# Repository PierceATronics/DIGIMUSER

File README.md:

# DIGIMUSER
DIGIMUSER is a digital vocal effect processor "stompbox" that applies a variety of real-time signal processing algorithms to alter the voice of a singer. DIGIMUSER takes a (1/4)" mono jack input from a dynamic microphone and outputs through another (1/4)" cable to an amplifier or to additional audio processing equipment. Since the effects applied by DIGIMUSER are performed digitally on a microcontroller, it can be reprogrammed to implement a wide collection of effecus such as filters, delays, distortions, and spatial effects. A standard bypass stomp button enables and disables the effect, a knob selects the type of applied effect, and a slider controls the intensity of the effect.
 
## Project Team Members
David Pierce Walker-Howell (EE), Luke kennard (COMPE), Danielle Stewart (COMPE), Suaod Alhajry (EE), Angel Martinez (COMPE)

## Contribute to this Project
Here are the guidelines to contribute to the project.

#### Branching
The development process for software or hardware must be done in a seperate branch from **main**. Once a software or hardware component is completed a pull request must be made before merging with **main**. The pull request must reviewed and approved before merging to main. 

Here is how to create a new branch off of main. Please use the following naming format for the branch **[Your_name]_[description_of_branch]**

```
Example

//Creates a new branch called "Pierce_I2S_software_development" off of the "main" branch
git checkout -b Pierce_I2S_software_development main
```

#### GIT workflow
Be sure to keep your branch (and the Repository) up-to-date on your local machine by performing pulls often (i.e. be sure to make a pull of the repo prior to making any new edits or commits). Also make sure to commit changes locally often and push those commits to the Github Repository often as well. Below is the typical workflow to follow

```
//Open a git bash or linux terminal and move to the DIGIMUSER project director

//You hop on your computer to begin working on the DIGIMUSER
//First, make sure to pull the repo

git pull

//Next, make sure you are in your development branch

git branch [THE_BRANCH_YOUR_ARE_DEVELOPING_IN]

//Work on coding and designing like on awesome engineer.

//Now you are at a good saving point, and would like to take a break for the day
//Commit your changes with a nice message about what you added/edited

git commit -m "Reworked the communication code for faster data transfer"

//You also want to save your code to the Github repo. So push those commits to the repo

git push origin [THE_BRANCH_YOU_ARE_DEVELOPING_IN]

```

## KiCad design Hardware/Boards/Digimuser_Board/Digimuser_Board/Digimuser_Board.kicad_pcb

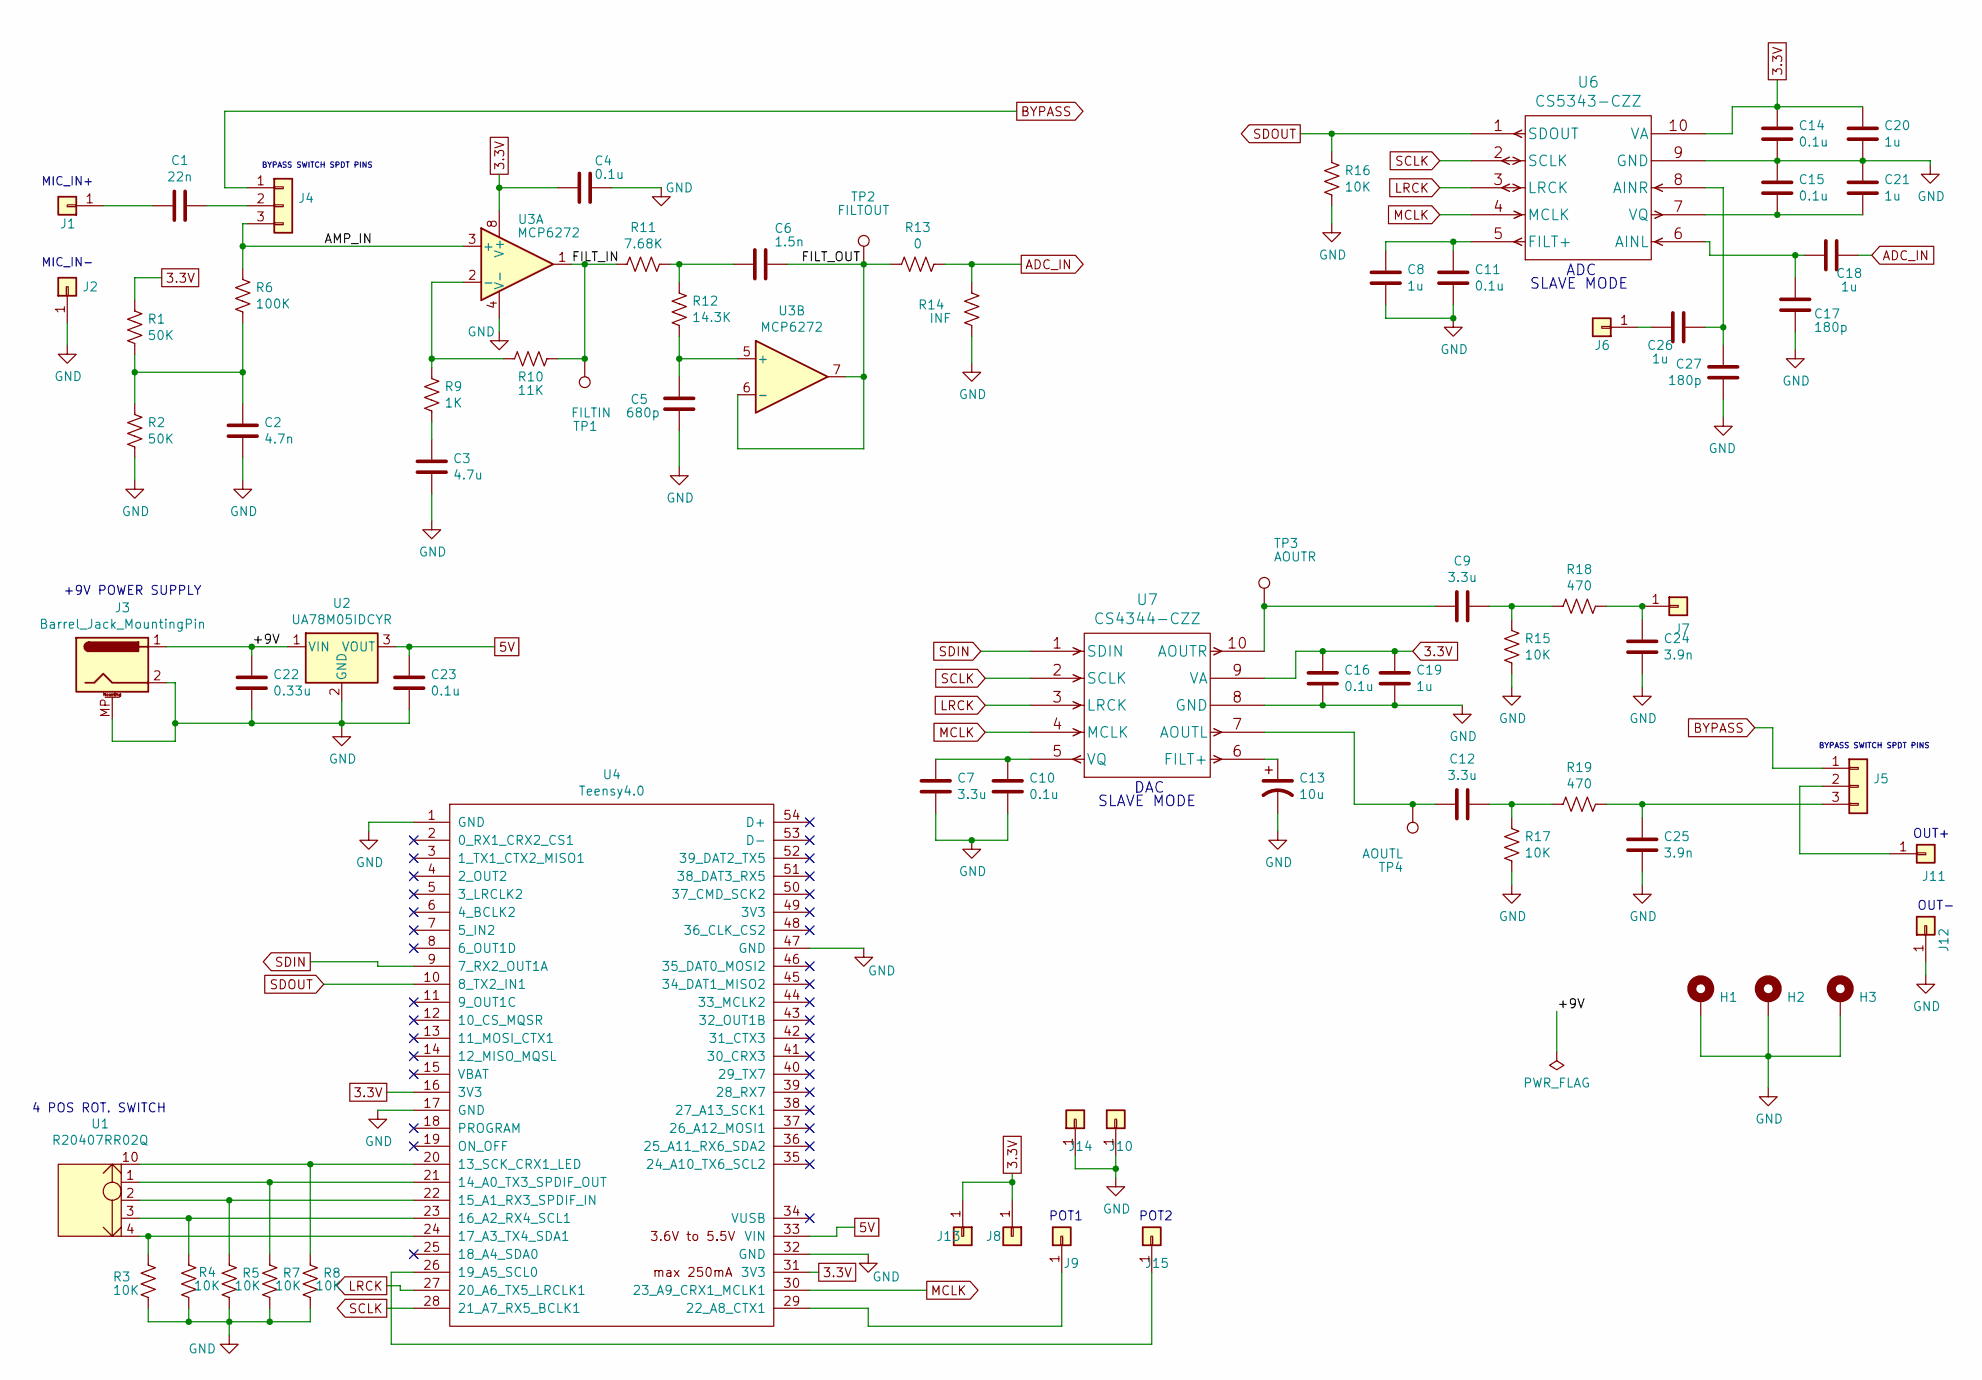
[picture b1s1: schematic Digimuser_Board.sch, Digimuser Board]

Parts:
C1: 22n; C_0805_2012Metric
C2: 4.7n; C_0805_2012Metric
C3: 4.7u; C_0805_2012Metric
C4, C10, C11, C14, C15, C16, C23: 0.1u; C_0805_2012Metric
C5: 680p; C_0805_2012Metric
C6: 1.5n; C_0805_2012Metric
C7, C9, C12: 3.3u; C_0805_2012Metric
C8, C18, C19, C20, C21, C26: 1u; C_0805_2012Metric
C13: 10u; C_Axial_L5.1mm_D3.1mm_P7.50mm_Horizontal
C17, C27: 180p; C_0805_2012Metric
C22: 0.33u; C_0805_2012Metric
C24, C25: 3.9n; C_0805_2012Metric
H1, H2, H3: MountingHole_Pad; MountingHole_2.2mm_M2_Pad
J1, J2, J6, J7, J8, J9, J10, J11, J12, J13, J14, J15: Conn_01x01; PinHeader_2.54mm_1x01_P2.54mm
J3: Barrel_Jack_MountingPin; BarrelJack_Horizontal
J4, J5: Conn_01x03; PinHeader_2.54mm_1x03_P2.54mm
R1, R2: 50K; R_0805_2012Metric
R3, R4, R5, R7, R8, R15, R16, R17: 10K; R_0805_2012Metric
R6: 100K; R_0805_2012Metric
R9: 1K; R_0805_2012Metric
R10: 11K; R_0805_2012Metric
R11: 7.68K; R_0805_2012Metric
R12: 14.3K; R_0805_2012Metric
R13: 0; R_0805_2012Metric
R14: INF; R_0805_2012Metric
R18, R19: 470; R_0805_2012Metric
TP1: FILTIN; TestPoint_Keystone_5019_Minature
TP2: FILTOUT; TestPoint_Keystone_5019_Minature
TP3: AOUTR; TestPoint_Keystone_5019_Minature
TP4: AOUTL; TestPoint_Keystone_5019_Minature
U1: R20407RR02Q
U2: UA78M05IDCYR; SOT-223-3_TabPin2
U3: MCP6272; SOIC127P600X175-8N
U4: Teensy4.0; Teensy40_HAT
U6: CS5343-CZZ
U7: CS4344-CZZ

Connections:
3.3V: C4.2, C14.1, C16.1, C19.1, C20.1, J8.1, J13.1, R1.1, U3.8 (V+), U4.16 (3V3), U4.31 (3V3), U6.10 (VA), U7.9 (VA)
5V: C23.1, U2.3 (VOUT), U4.33 (VIN)
/+9V: C22.1, J3.1, U2.1 (VIN)
/AMP_IN: J4.3, R6.1, U3.3 (+)
/FILT_IN: R10.1, R11.2, TP1.1, U3.1
/FILT_OUT: C6.1, R13.2, TP2.1, U3.6 (-), U3.7
ADC_IN: C18.1, R13.1, R14.2
BYPASS: J4.1, J5.1
GND: C2.2, C3.2, C4.1, C5.2, C7.2, C8.2, C10.2, C11.2, C13.2, C14.2, C15.1, C16.2, C17.2, C19.2, C20.2, C21.1, C22.2, C23.2, C24.2, C25.2, C27.2, H1.1, H2.1, H3.1, J2.1, J3.2, J3.MP (MountPin), J10.1, J12.1, J14.1, R2.2, R3.2, R4.2, R5.2, R7.2, R8.2, R14.1, R15.2, R16.2, R17.2, U2.2 (GND), U3.4 (V-), U4.1 (GND), U4.17 (GND), U4.32 (GND), U4.47 (GND), U6.9 (GND), U7.8 (GND)
LRCK: U4.27 (20_A6_TX5_LRCLK1), U6.3 (LRCK), U7.3 (LRCK)
MCLK: U4.30 (23_A9_CRX1_MCLK1), U6.4 (MCLK), U7.4 (MCLK)
unnamed: C1.1, J4.2
unnamed: C1.2, J1.1
unnamed: C2.1, R1.2, R2.1, R6.2
unnamed: C3.1, R9.2
unnamed: C5.1, R12.2, U3.5 (+)
unnamed: C6.2, R11.1, R12.1
unnamed: C9.1, R15.1, R18.2
unnamed: C9.2, TP3.1, U7.10 (AOUTR)
unnamed: C7.1, C10.1, U7.5 (VQ)
unnamed: C8.1, C11.1, U6.5 (FILT+)
unnamed: C12.1, R17.1, R19.2
unnamed: C12.2, TP4.1, U7.7 (AOUTL)
unnamed: C13.1, U7.6 (FILT+)
unnamed: C15.2, C21.2, U6.7 (VQ)
unnamed: C17.1, C18.2, U6.6 (AINL)
unnamed: C24.1, J7.1, R18.1
unnamed: C25.1, J5.3, R19.1
unnamed: C26.1, J6.1
unnamed: C26.2, C27.1, U6.8 (AINR)
unnamed: J9.1, U4.29 (22_A8_CTX1)
unnamed: J5.2, J11.1
unnamed: J15.1, U4.26 (19_A5_SCL0)
unnamed: R3.1, U1.4, U4.24 (17_A3_TX4_SDA1)
unnamed: R4.1, U1.3, U4.23 (16_A2_RX4_SCL1)
unnamed: R5.1, U1.2, U4.22 (15_A1_RX3_SPDIF_IN)
unnamed: R7.1, U1.1, U4.21 (14_A0_TX3_SPDIF_OUT)
unnamed: R8.1, U1.10, U4.20 (13_SCK_CRX1_LED)
unnamed: R9.1, R10.2, U3.2 (-)
SCLK: U4.28 (21_A7_RX5_BCLK1), U6.2 (SCLK), U7.2 (SCLK)
SDIN: U4.9 (7_RX2_OUT1A), U7.1 (SDIN)
SDOUT: R16.1, U4.10 (8_TX2_IN1), U6.1 (SDOUT)

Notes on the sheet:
BYPASS SWITCH SPDT PINS
MIC_IN+
MIC_IN-
ADC
SLAVE MODE
DAC
+9V POWER SUPPLY
4 POS ROT. SWITCH
OUT+
OUT-
POT1
POT2

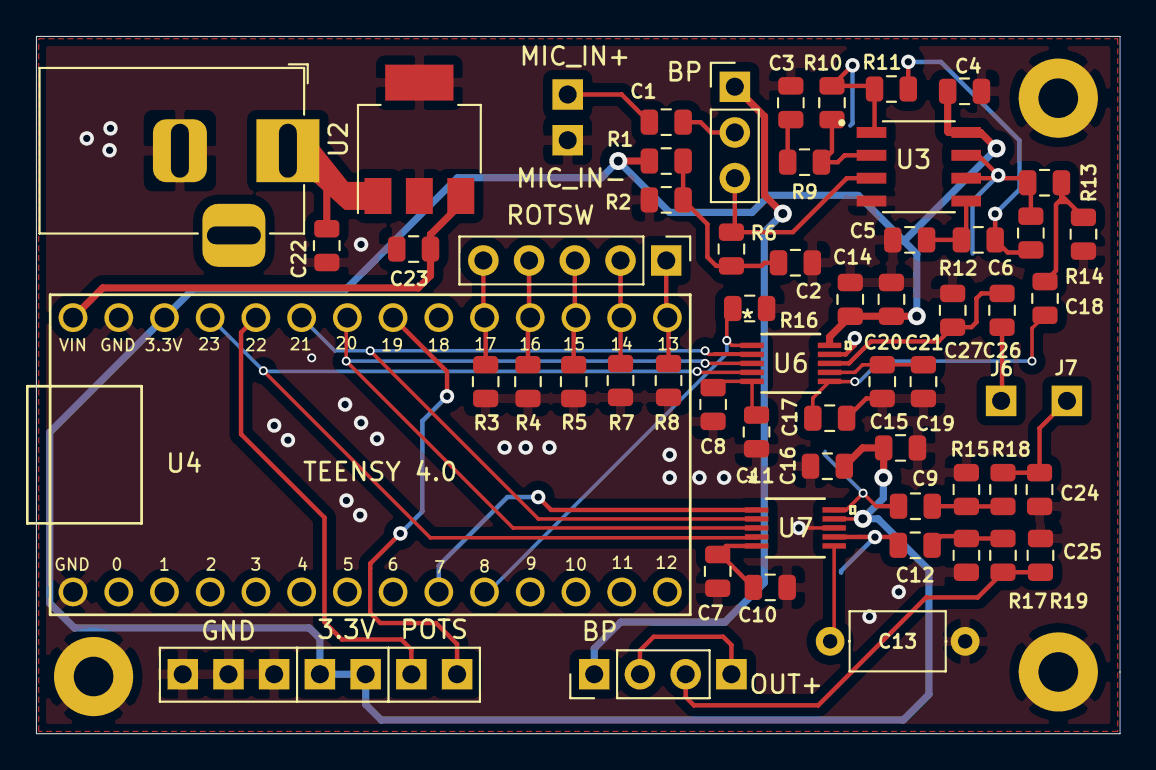
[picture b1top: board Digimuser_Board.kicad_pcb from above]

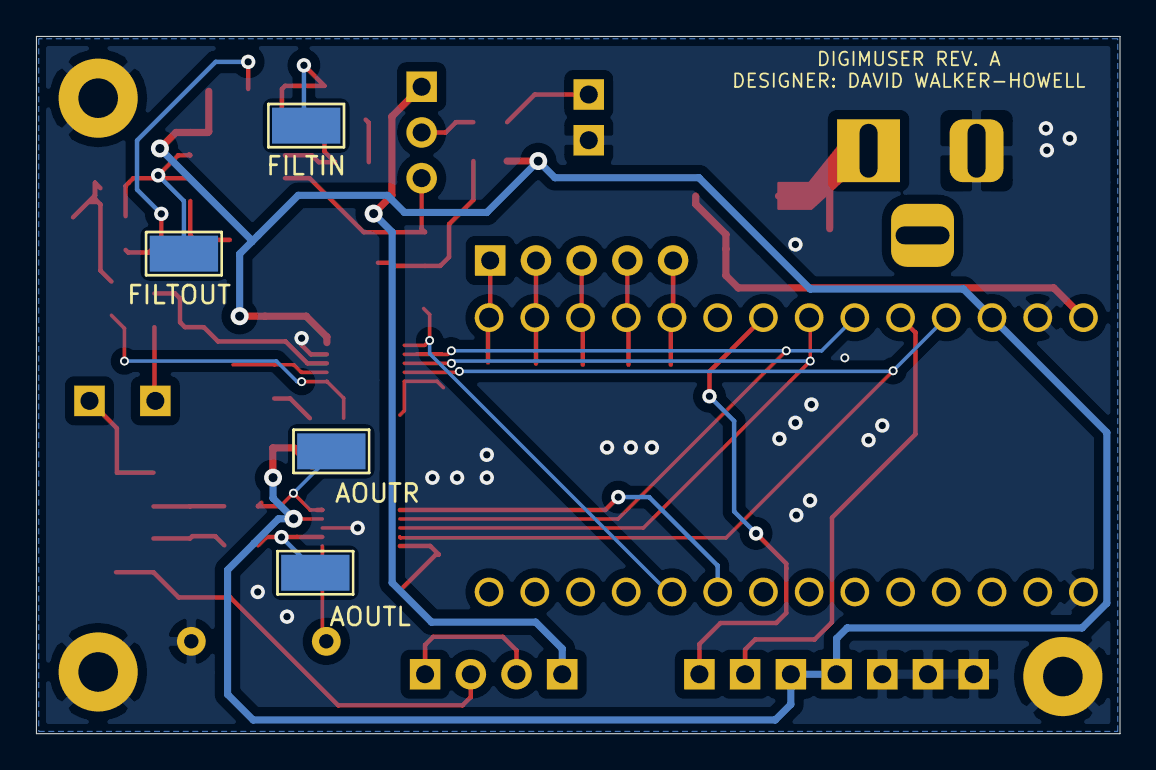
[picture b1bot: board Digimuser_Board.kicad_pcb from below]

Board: 2 copper layers, 60.2 x 38.7 mm, 74 parts (4 on the bottom side), 42 nets.

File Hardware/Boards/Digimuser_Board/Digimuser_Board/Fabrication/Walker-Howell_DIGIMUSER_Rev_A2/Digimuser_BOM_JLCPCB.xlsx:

Comment | Designator | Footprint | LCSC Part #（optional）
22nF | C1 | 0805_C | C1729 | x
51KΩ | R1, R2 | 0805_R | C17737 | x
100KΩ | R6 | 0805_R | C17407 | x
4.7nF | C2 | 0805_C | C1744 | x
4.7uF | C3 | 0805_C | C1779 | x
1KΩ | R9 | 0805_R | C17513 | x
11KΩ | R10 | 0805_R | C17429 | x
100nF | C4, C10, C11, C14, C15, C16, C23 | 0805_C | C49678 | x
7.68KΩ | R11 | 0805_R | C30041 | x
14.3KΩ | R12 | 0805_R | C17456 | x
680pF | C5 | 0805_C | C53150 | x
1.5nF | C6 | 0805_C | C1717 | x
10KΩ | R3, R4, R5, R7, R8, R15, R16, R17 | 0805_R | C17414 | x
1uF | C8, C18, C19, C20, C21, C26 | 0805_C | C28323 | x
180pF | C17, C27 | 0805_C | C62914 | x
3.3uF | C7, C9, C12 | 0805_C | C159775 | x
470Ω | R18, R19 | 0805_R | C17710 | x
3.3nF | C24, C25 | 0805_C | C53175 | x
0.33uF | C22 | 0805_C | C1740 | x

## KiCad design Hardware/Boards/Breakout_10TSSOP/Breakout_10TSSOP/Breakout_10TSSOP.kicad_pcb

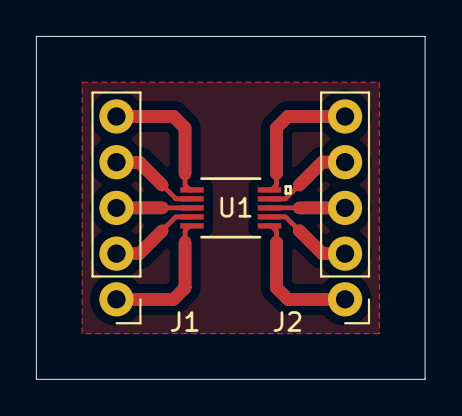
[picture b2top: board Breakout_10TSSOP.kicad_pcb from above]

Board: 2 copper layers, 21.6 x 19.0 mm, 4 parts (1 on the bottom side), 10 nets.

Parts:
J1, J2: Conn_01x05_Male; PinHeader_1x05_P2.54mm_Vertical
U1, U1#2: CS5343-CZZ

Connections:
1: J1.5, U1.5, U1#2.1
2: J1.4, U1.4, U1#2.2
3: J1.3, U1.3, U1#2.3
4: J1.2, U1.2, U1#2.4
5: J1.1, U1.1, U1#2.5
6: J2.1, U1.10, U1#2.6
7: J2.2, U1.9, U1#2.7
8: J2.3, U1.8, U1#2.8
9: J2.4, U1.7, U1#2.9
10: J2.5, U1.6, U1#2.10

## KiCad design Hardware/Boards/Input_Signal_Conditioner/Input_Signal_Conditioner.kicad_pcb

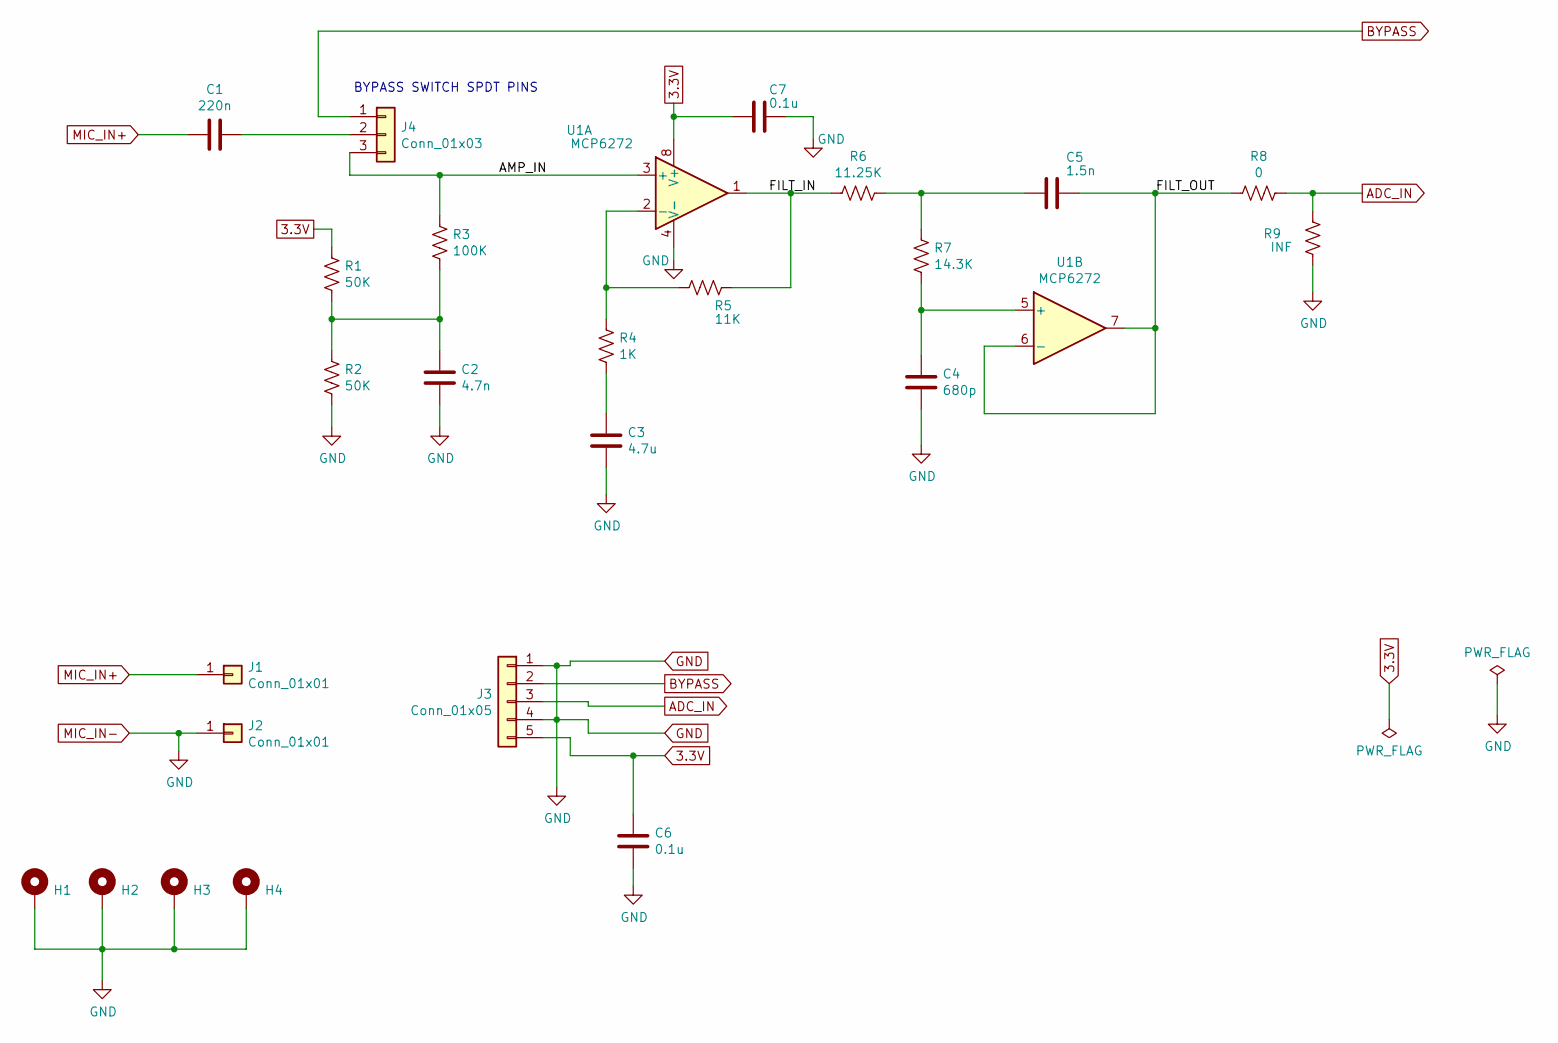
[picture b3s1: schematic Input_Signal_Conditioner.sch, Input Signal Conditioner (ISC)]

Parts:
C1: 220n; C_Disc_D7.5mm_W4.4mm_P5.00mm
C2: 4.7n; C_Disc_D7.5mm_W4.4mm_P5.00mm
C3: 4.7u; C_Disc_D7.5mm_W4.4mm_P5.00mm
C4: 680p; C_Disc_D7.5mm_W4.4mm_P5.00mm
C5: 1.5n; C_Disc_D7.5mm_W4.4mm_P5.00mm
C6, C7: 0.1u; C_Disc_D7.5mm_W4.4mm_P5.00mm
H1, H2, H3, H4: MountingHole_Pad; MountingHole_3.2mm_M3_Pad
J1, J2: Conn_01x01; PinSocket_1x01_P2.54mm_Vertical
J3: Conn_01x05; PinSocket_1x05_P2.54mm_Vertical
J4: Conn_01x03; PinSocket_1x03_P2.54mm_Vertical
R1, R2: 50K; R_Axial_DIN0207_L6.3mm_D2.5mm_P10.16mm_Horizontal
R3: 100K; R_Axial_DIN0207_L6.3mm_D2.5mm_P10.16mm_Horizontal
R4: 1K; R_Axial_DIN0207_L6.3mm_D2.5mm_P10.16mm_Horizontal
R5: 11K; R_Axial_DIN0207_L6.3mm_D2.5mm_P10.16mm_Horizontal
R6: 11.25K; R_Axial_DIN0207_L6.3mm_D2.5mm_P10.16mm_Horizontal
R7: 14.3K; R_Axial_DIN0207_L6.3mm_D2.5mm_P10.16mm_Horizontal
R8: 0; R_Axial_DIN0207_L6.3mm_D2.5mm_P10.16mm_Horizontal
R9: INF; R_Axial_DIN0207_L6.3mm_D2.5mm_P10.16mm_Horizontal
U1: MCP6272; DIP-8_W7.62mm

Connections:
3.3V: C6.1, C7.2, J3.5, R1.1, U1.8 (V+)
/AMP_IN: J4.3, R3.1, U1.3 (+)
/FILT_IN: R5.1, R6.2, U1.1
/FILT_OUT: C5.1, R8.2, U1.6 (-), U1.7
ADC_IN: J3.3, R8.1, R9.2
BYPASS: J3.2, J4.1
GND: C2.2, C3.2, C4.2, C6.2, C7.1, H1.1, H2.1, H3.1, H4.1, J2.1, J3.1, J3.4, R2.2, R9.1, U1.4 (V-)
MIC_IN+: C1.2, J1.1
unnamed: C1.1, J4.2
unnamed: C2.1, R1.2, R2.1, R3.2
unnamed: C3.1, R4.2
unnamed: C4.1, R7.2, U1.5 (+)
unnamed: C5.2, R6.1, R7.1
unnamed: R4.1, R5.2, U1.2 (-)

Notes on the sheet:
BYPASS SWITCH SPDT PINS

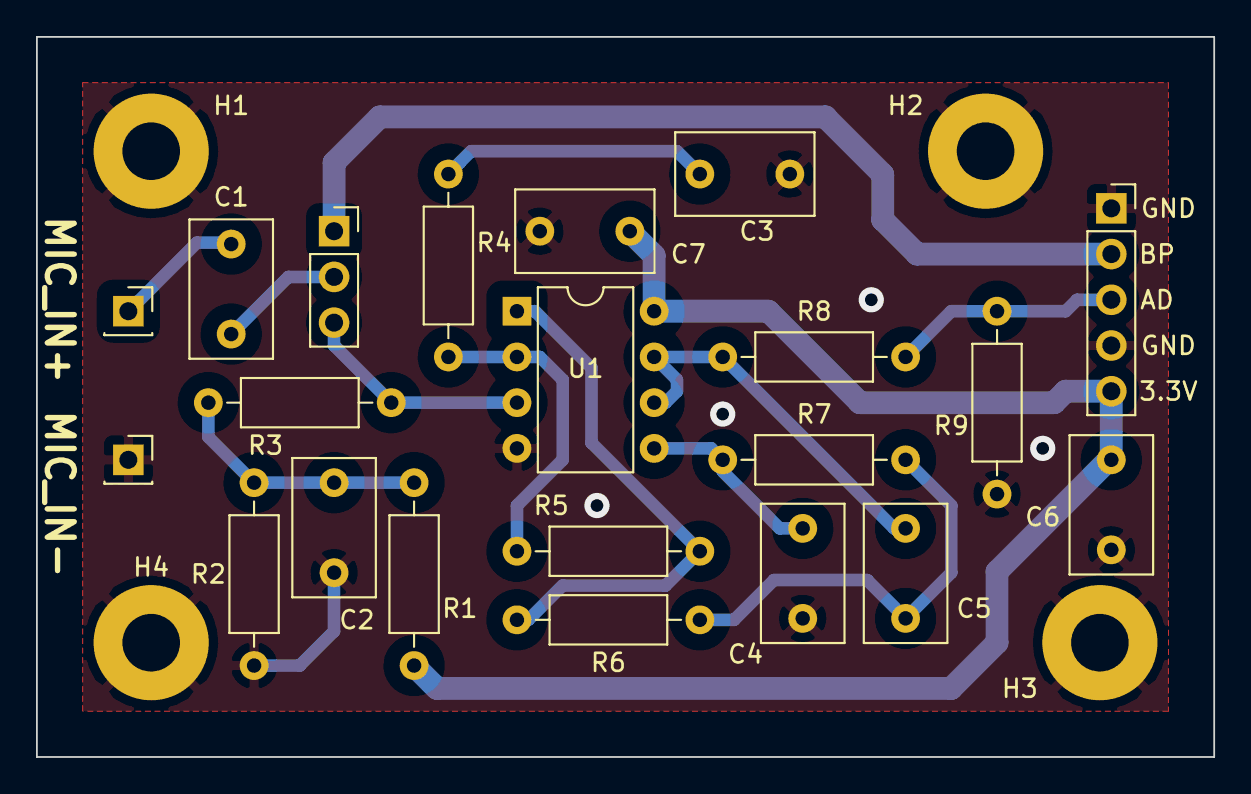
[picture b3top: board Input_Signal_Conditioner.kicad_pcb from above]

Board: 2 copper layers, 65.4 x 40.0 mm, 25 parts (0 on the bottom side), 14 nets.

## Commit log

2020-10-23 ISC schematic design and ISC LTSpice simulation.
2020-10-23 Assigned PCB footprints to ISC. Started layout of the PCB, traces still need to be routed.
2020-10-28 Redesigned the ISC LPF filter to a new cutoff frequency. Also began documentation of the ISC design. Updated the LTSpice simulation of the ISC to reflect LPF changes. Choose an Op-amp for the design.
2020-10-29 Updated the LTSpice sim of the ISC to use audio (.wav) files! Also worked on documentation of ISC.
2020-10-29 Redid the layout of the PCB to be THT components. Layout needs review, then it is ready to print.
2020-10-30 Added mounting holes to the Input Signal Conditioner PCB. Also began citation information for ISC documentation.
2020-11-02 Made edits suggested by Mark to the ISC pcb. Sent the board for Milling.
2020-11-03 Designed the breakout board for the 10TSSOP footprint of the ADC and DAC. Needs review before manufacturing.
2020-11-03 Revised PCB for the 10TSSOP Breakout board. Sent in for fabrication.
2020-11-10 Updated an incorrect resistor value on the schematic (resistor R6).
2020-11-11 Edited the LTSpice simulation to use th 22nF AC coupling capacitor.
2020-11-13 Described git contribution workflow
2020-11-13 Updated the ISC documentation with Validation data.
2020-11-13 Started the schematic design of the DIGIMUSER Board, the final PCB design.
2020-11-13 Finished the electrical connections to the ADC on the schematic.
2020-11-18 Added the DAC, Output Signal Conditioner, and 5V linear regulator.
2020-11-19 Added the rotary switch and slider pot to the schematic. Created custom symbol for the rotary switch.
2020-11-28 Assigned PCB footprints to all the components. Some components may need footprints revised.
2020-11-28 Started the PCB layout. Also had to find a new voltage regulator.
2020-11-28 Completed most of the PCB layout organization. Still have a lot of work on it.
2020-11-28 Continued PCB layout.
2020-11-29 Finished the first revision of the PCB layout. Needs reviewing.
2020-12-01 Last save before making circuit revisions.
2020-12-01 Did a re-layout of the PCB and redid the schematic.Ready for review.
2020-12-02 Relabled Testpoints on PCB.
2020-12-02 Added pin connection for a second potentiometer.
2020-12-03 Sent board out for review. Received feedback and made changes to the PCB layout accordingly. Changes include: Pin headers spaced 0.1in, Labeling Teensy connection pins, updating voltage regulator GND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
2020-12-23 Finished final details for first prototype.
2021-02-01 Added a basic led_blink test code for testing the Teensy 4.0
2021-02-02 Added all files for DAC. Will need massive clean up
2021-02-03 Created the firmware file structure.
2021-02-18 Added DAC driver files along with main header DIGILIB.h
2021-02-18 notes for DIGILIB.h
2021-02-24 Learning how to use git
2021-02-25 Cleaned up repo
2021-03-01 Wrote the CS4344 test sketch for the Teensy 4.0 to be used for Electrical validations that the DAC works.
2021-03-01 Wrote the cs5343_test sketch to test the cs5343 ADC works.
2021-03-02 ADC/DAC passthroguh enabled. Effects testing included in main.
2021-03-04 Added completed dist effect
2021-03-04 Tremolo Class and Header
2021-03-13 Prototyped Custom effect structure. Compliles but is untested.
2021-03-13 Tested basic AmplifierEffects class. This proves how to structure custom effects to integrate with the Teensy4.0 audio lib.
2021-03-14 Revised the amplify effect to use float operation and a pot to dynamically control amplification.
2021-03-17 Updated the Header/CPP to follow the new format
2021-03-19 Tremolo effect integrated, not tested
2021-03-24 Tremolo effect integrated and tested with working potentiometer
2021-03-24 Cleaned up main ino file. Sine_test and waveform_test .ino files created
2021-03-25 Distortion effect integrated, not tested.
2021-03-25 Fixed bugs, added libraries
2021-03-26 LTSpice simulation of stomp button pop fix
2021-03-26 Reorganized the file structure to be cleaner. Made a simple iir comb filter based reverb in MATLAB.
2021-03-27 Wrote untested code for fixed-point based reverb using a single IIR Comb filter...needs testing and debugging.
2021-03-29 Got basic reverb working on the DIGIMUSER using fixed point
2021-03-29 Revised file structure...to run the examples, the DIGIMUSER folder must be in the Arduino/Libraries directory.
2021-03-29 Updated the reverb effect in matlab to have delay blocks that are multiples of 16.
2021-03-29 Added the MIT license to the top of all the code. Finished writing the reverb effect with 4 IIR comb filters...needs testing.
2021-03-29 Got Reverb working very well with 4 IIR Comb filters.
2021-03-30 Sample the pot to 16-bits (15 fractional). This controls the attenuation factor for the IIR comb filters. Needs testing.
2021-03-30 Tested some guitar sounds in MATLAB.
2021-03-30 More investigation into stomp button pop.
2021-03-30 Distortion effect integrated. Works with phone audio input but not mic
2021-03-30 Finalized version of the reverb effect. This is the best sounding one yet!
2021-03-31 Added pot_test example, as required by the electrical validation document.
2021-04-01 Included rotary switch test file
2021-04-01 Added Flanger files
2021-04-01 Integrated reverb, distortion, and tremolo. First successful full system tests.
2021-04-02 Added the rotary switch test arduino sketch.

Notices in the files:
parts and their libraries:
Copyright 2016 Accelerated Designs. All rights reserved.
